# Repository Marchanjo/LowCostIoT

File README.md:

# LowCostIoT
Hardware, Embedded software and Android App for Internet of Things, with low cost components.

Mapa do projeto
---------------
* **/TOM2015/Firmware** - Firmware e Código ESP8266 (Tomada e Interrptor)
* **/TOM2015/Hardware** - Arquivos de design (Eagle) da PCB, esquemáticos e gerbers (Tomada e Interrptor)
* **/TOM2015/App** - Código da aplicação Android
* **/TOM2015/Bin** - Arquivos binários (APK)

Licença
-------
O hardware e o software estão disponiveis em [Creative Commons Atribuição-NãoComercial-CompartilhaIgual 4.0 Internacional. License.](http://creativecommons.org/licenses/by-nc-sa/4.0/)
 
The hardware and the software are released under [Creative Commons Atribuição-NãoComercial-CompartilhaIgual 4.0 Internacional. License.](http://creativecommons.org/licenses/by-nc-sa/4.0/)

Distribuido como está, nenhuma garantia é dada.

Distributed as-is; no warranty is given.

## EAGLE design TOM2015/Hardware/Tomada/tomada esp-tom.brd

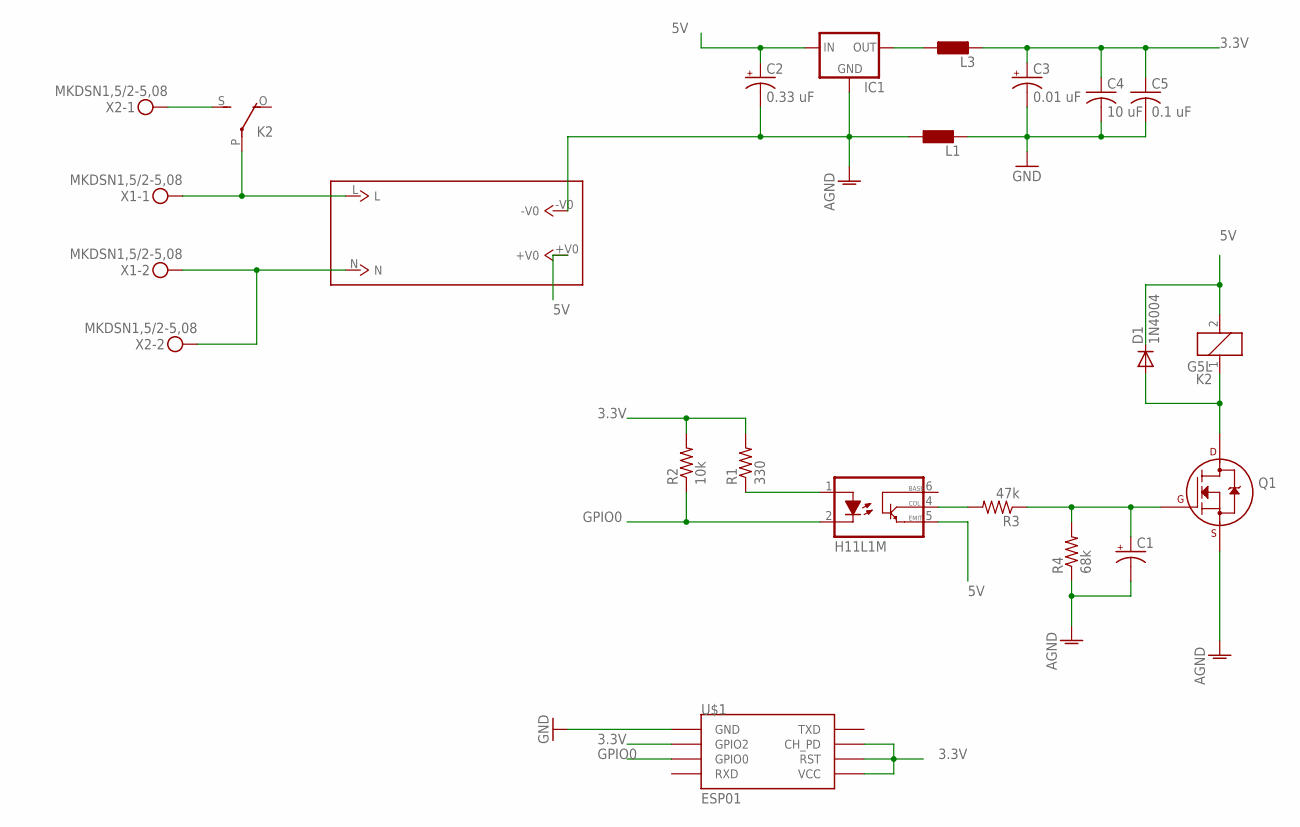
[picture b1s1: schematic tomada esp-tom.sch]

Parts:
C1: CPOL-USE2-5; E2-5
C2: 0.33 uF; E2-5
C3: 0.01 uF; E2-5
C4: 10 uF; C025-024X044
C5: 0.1 uF; C025-024X044
D1: 1N4004; DO41-10
IC1: 78LXX
K2: G5L; G5LE
L1, L3: L0207/10; 0207/10
OK1: H11L1M; DIL06
Q1: 2N7000_TO92; TO-92
R1: 330; 0204/7
R2: 10k; 0204/7
R3: 47k; 0204/7
R4: 68k; 0204/7
U$1: ESP01
U$2: NA03-T2S05
X1, X2: MKDSN1,5/2-5,08

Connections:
3.3V: C3.+, C4.1, C5.1, L3.2, R1.2, R2.2, U$1.CH_PD, U$1.GPIO2, U$1.RST, U$1.VCC
5V: C2.+, D1.C, IC1.IN, K2.2, OK1.5 (GND), U$2.+V0
AGND: C1.-, C2.-, IC1.GND, L1.1, Q1.1 (S), R4.1, U$2.-V0
GND: C3.-, C4.2, C5.2, L1.2, U$1.GND
GPIO0: OK1.2 (C), R2.1, U$1.GPIO0
unnamed: OK1.1 (A), R1.1
unnamed: C1.+, Q1.2 (G), R3.1, R4.2
unnamed: OK1.4 (OUT), R3.2
unnamed: D1.A, K2.1, Q1.3 (D)
unnamed: K2.S, X2.1
unnamed: K2.P, U$2.L, X1.1
unnamed: U$2.N, X1.2, X2.2
unnamed: IC1.OUT, L3.1
VCC: OK1.6 (VCC)

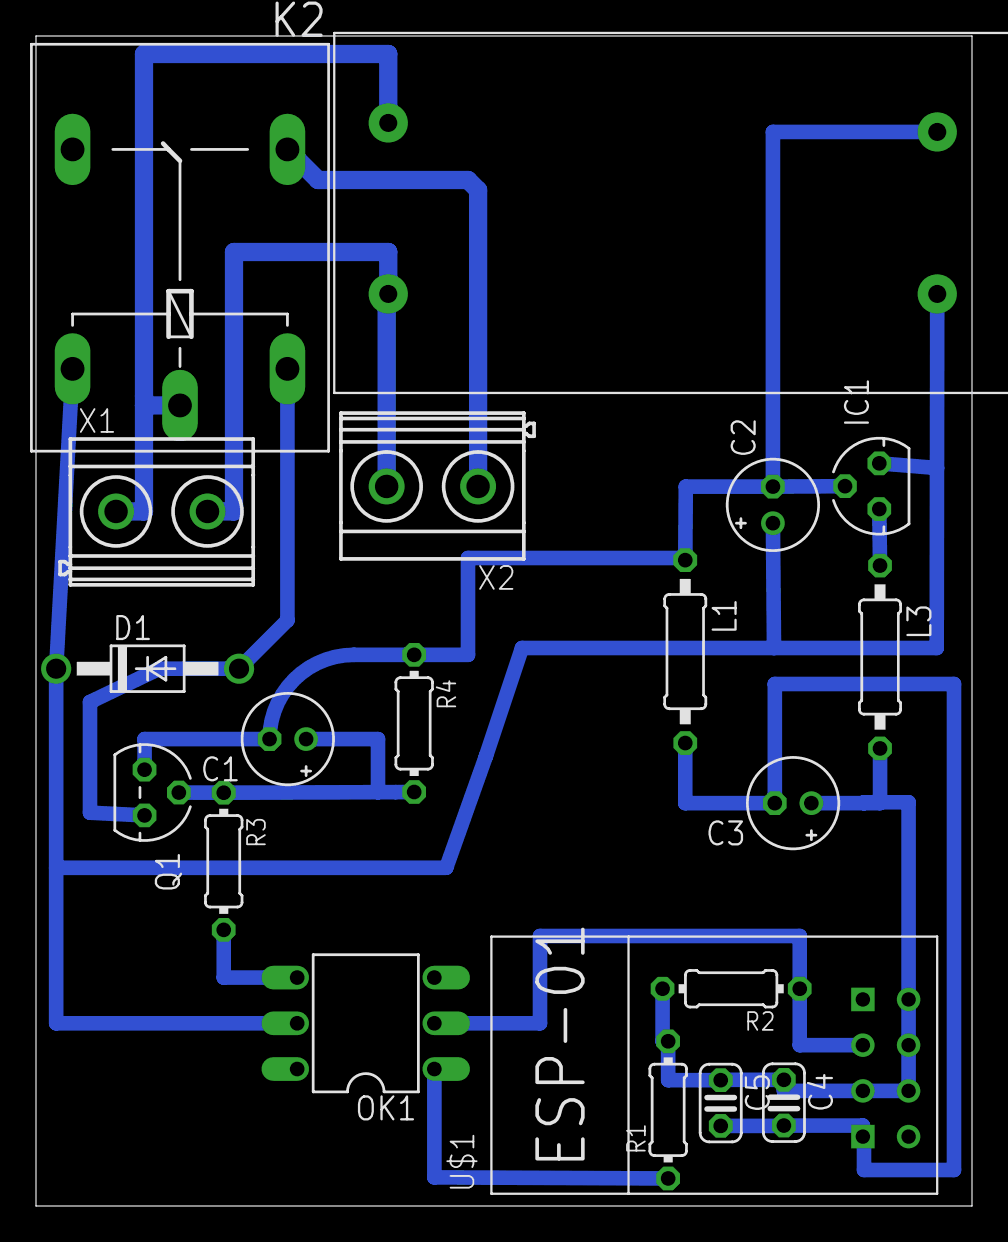
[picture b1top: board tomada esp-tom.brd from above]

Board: 2 copper layers, 52.0 x 65.0 mm, 20 parts (0 on the bottom side), 13 nets.

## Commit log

2015-11-08 aplicativo do usado no TOM
2015-11-08 novo nome pasta
2015-11-09 Organização da Estrutura de diretórios
    Criada uma estrutura na raíz para tudo que foi apresentado no TOM 2015.
2015-11-10 Versão final do tom
    Versão final do Tom com as ligações do esp corretas e o desenho correto
    do componente TIL111
2015-11-10 Adicionadas as imagens do esquemático
    Adicionadas as imagens do esquemático tanto do interruptor, quanto da
    tomada
2015-11-10 Atualização do ReadMe
    Inclui o mapa do projetono Read Me
2015-11-10 Primeira versao: TOM2015
2015-11-11 bin/ e apk adicionados
2015-11-13 modificação do readme do app
2015-11-13 License
    Atribuição da licença
2015-11-13 Descrição da Licença no ReadMe
    Descrição da Licença no ReadMe
2015-11-13 Correção no texto
2015-11-26 mais informações para reutilização do código
2017-02-13 Prototipo funcional
